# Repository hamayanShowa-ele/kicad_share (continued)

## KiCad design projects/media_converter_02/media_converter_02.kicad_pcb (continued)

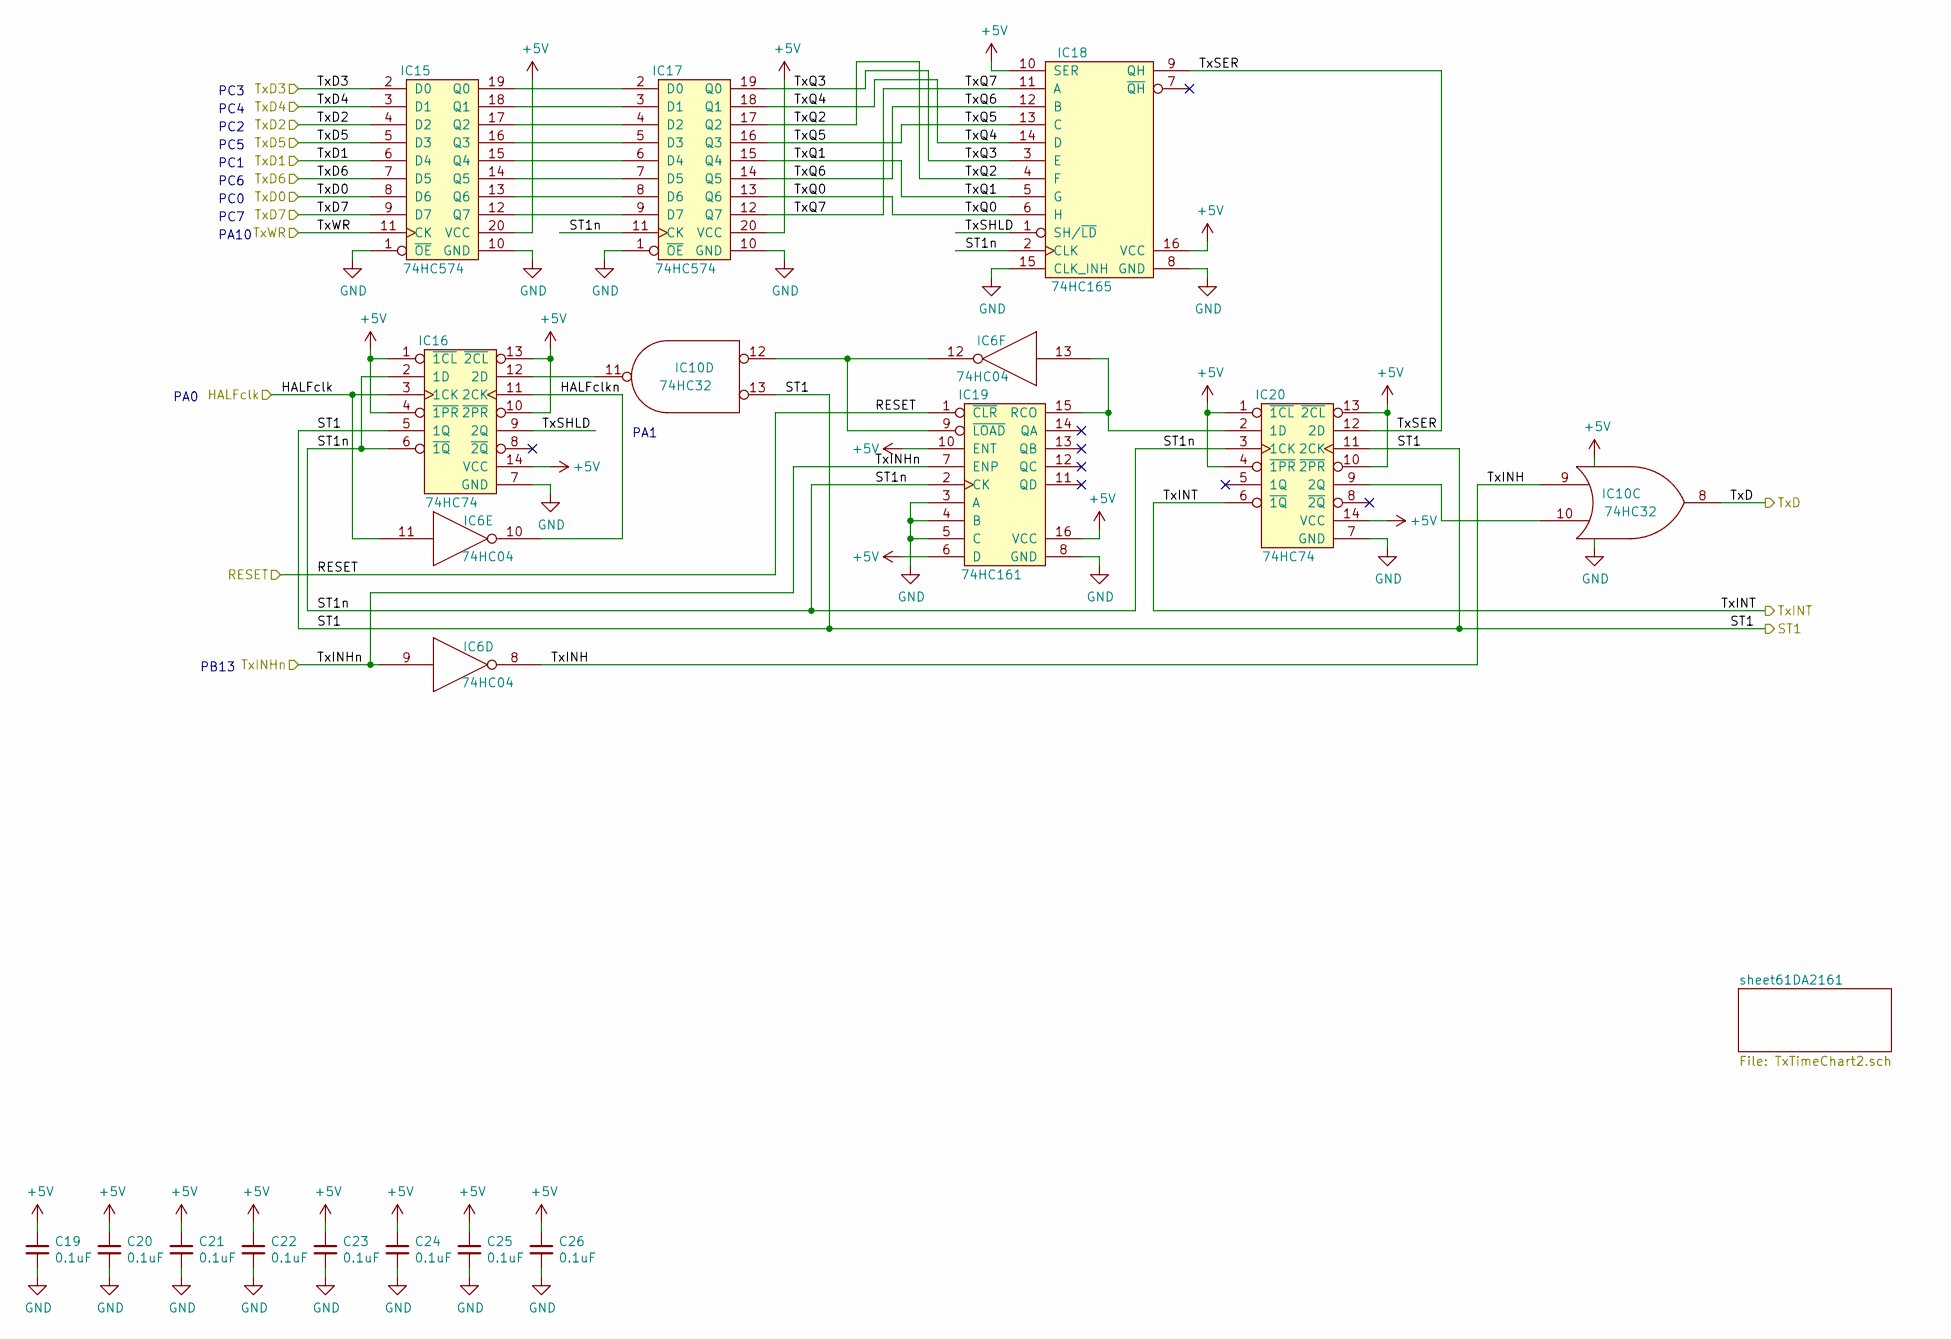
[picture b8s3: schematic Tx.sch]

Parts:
C19, C20, C21, C22, C23, C24, C25, C26: 0.1uF; C_0603
IC6: 74HC04; IC_DIP-14_W7.62mm
IC10: 74HC32; IC_DIP-14_W7.62mm
IC15, IC17: 74HC574; ic_DIP-20_W7.62mm
IC16, IC20: 74HC74; IC_DIP-14_W7.62mm
IC18: 74HC165; ic_DIP-16_W7.62mm
IC19: 74HC161; ic_DIP-16_W7.62mm

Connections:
+5V: C19.1, C20.1, C21.1, C22.1, C23.1, C24.1, C25.1, C26.1, IC6.14 (VCC), IC10.14 (VCC), IC15.20 (VCC), IC16.1 (~1CL), IC16.4 (~1PR), IC16.10 (~2PR), IC16.13 (~2CL), IC16.14 (VCC), IC17.20 (VCC), IC18.10 (SER), IC18.16 (VCC), IC19.6 (D), IC19.10 (ENT), IC19.16 (VCC), IC20.1 (~1CL), IC20.4 (~1PR), IC20.10 (~2PR), IC20.13 (~2CL), IC20.14 (VCC); also elsewhere on the board
/HALFclk: IC6.11, IC16.3 (1CK); also elsewhere on the board
/RSTn: IC19.1 (~CLR); also elsewhere on the board
/ST1: IC10.13, IC16.5 (1Q), IC20.11 (2CK); also elsewhere on the board
/Tx/HALFclkn: IC6.10, IC16.11 (2CK)
/Tx/ST1n: IC16.2 (1D), IC16.6 (~1Q), IC17.11 (CK), IC18.2 (CLK), IC19.2 (CK), IC20.3 (1CK)
/Tx/TxINH: IC6.8, IC10.9
/Tx/TxQ0: IC17.13 (Q6), IC18.6 (H)
/Tx/TxQ1: IC17.15 (Q4), IC18.5 (G)
/Tx/TxQ2: IC17.17 (Q2), IC18.4 (F)
/Tx/TxQ3: IC17.19 (Q0), IC18.3 (E)
/Tx/TxQ4: IC17.18 (Q1), IC18.14 (D)
/Tx/TxQ5: IC17.16 (Q3), IC18.13 (C)
/Tx/TxQ6: IC17.14 (Q5), IC18.12 (B)
/Tx/TxQ7: IC17.12 (Q7), IC18.11 (A)
/Tx/TxSER: IC18.9 (QH), IC20.12 (2D)
/Tx/TxSHLD: IC16.9 (2Q), IC18.1 (SH/~LD)
/TxD: IC10.8; also elsewhere on the board
/TxD0: IC15.8 (D6); also elsewhere on the board
/TxD1: IC15.6 (D4); also elsewhere on the board
/TxD2: IC15.4 (D2); also elsewhere on the board
/TxD3: IC15.2 (D0); also elsewhere on the board
/TxD4: IC15.3 (D1); also elsewhere on the board
/TxD5: IC15.5 (D3); also elsewhere on the board
/TxD6: IC15.7 (D5); also elsewhere on the board
/TxD7: IC15.9 (D7); also elsewhere on the board
/TxINHn: IC6.9, IC19.7 (ENP); also elsewhere on the board
/TxINT: IC20.6 (~1Q); also elsewhere on the board
/TxWR: IC15.11 (CK); also elsewhere on the board
GND: C19.2, C20.2, C21.2, C22.2, C23.2, C24.2, C25.2, C26.2, IC6.7 (GNDA), IC10.7 (GND), IC15.1 (~OE), IC15.10 (GND), IC16.7 (GND), IC17.1 (~OE), IC17.10 (GND), IC18.8 (GND), IC18.15 (CLK_INH), IC19.3 (A), IC19.4 (B), IC19.5 (C), IC19.8 (GND), IC20.7 (GND); also elsewhere on the board
unnamed: IC10.10, IC20.9 (2Q)
unnamed: IC10.11, IC16.12 (2D)
unnamed: IC6.12, IC10.12, IC19.9 (~LOAD)
unnamed: IC15.12 (Q7), IC17.9 (D7)
unnamed: IC15.13 (Q6), IC17.8 (D6)
unnamed: IC15.14 (Q5), IC17.7 (D5)
unnamed: IC15.15 (Q4), IC17.6 (D4)
unnamed: IC15.16 (Q3), IC17.5 (D3)
unnamed: IC15.17 (Q2), IC17.4 (D2)
unnamed: IC15.18 (Q1), IC17.3 (D1)
unnamed: IC15.19 (Q0), IC17.2 (D0)
unnamed: IC6.13, IC19.15 (RCO), IC20.2 (1D)

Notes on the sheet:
PA0
PA1
PA10
PC7
PC6
PC5
PC4
PC3
PC2
PC1
PC0
PB13

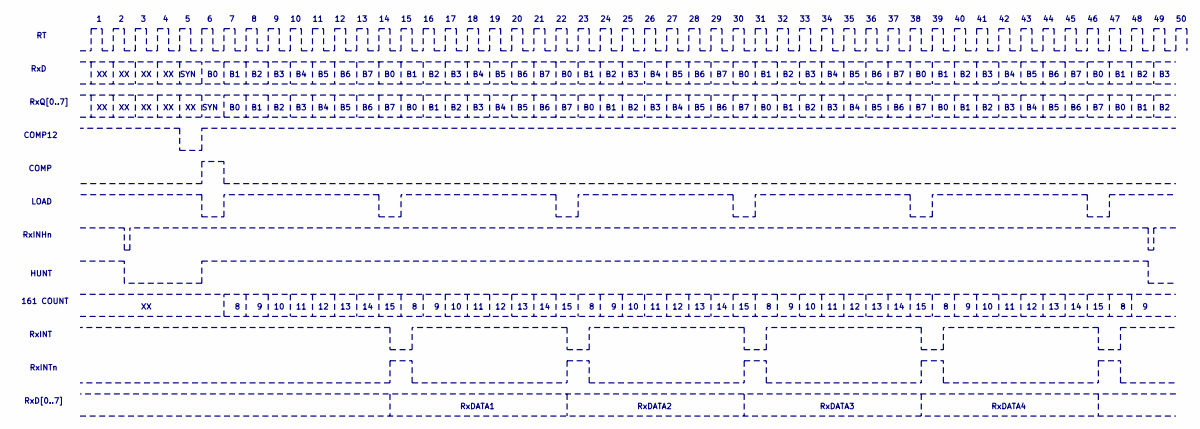
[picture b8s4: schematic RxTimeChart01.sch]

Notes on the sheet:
COMP12
161 COUNT
LOAD
HUNT
RxD
SYN
RxQ[0..7]
RxINT
RxINTn
RxDATA1
RxDATA2
RxDATA3
RxDATA4
RxD[0..7]
RxINHn
COMP

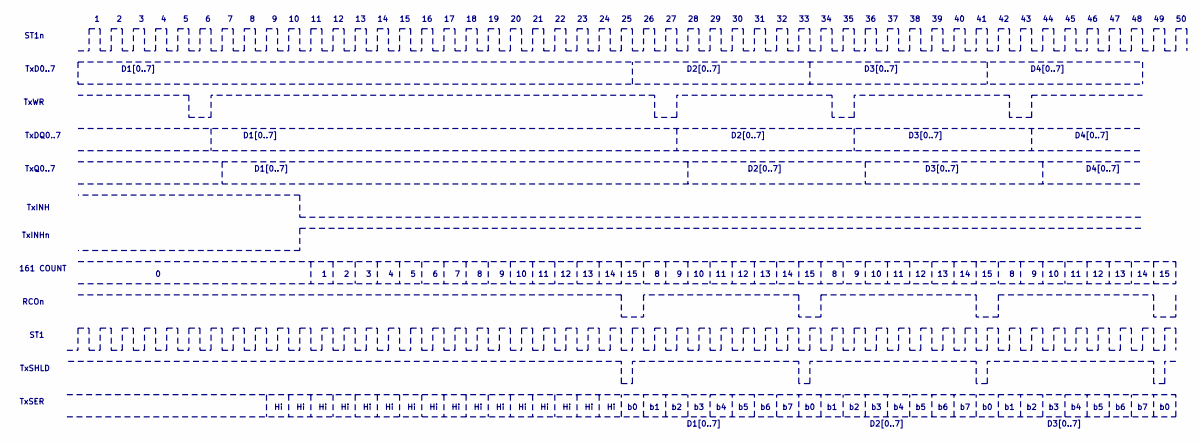
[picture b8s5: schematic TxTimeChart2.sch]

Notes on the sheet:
ST1n
TxD0..7
D1[0..7]
TxWR
TxDQ0..7
TxQ0..7
TxINH
TxINHn
161 COUNT
RCOn
ST1
TxSHLD
TxSER
D2[0..7]
D3[0..7]
D4[0..7]

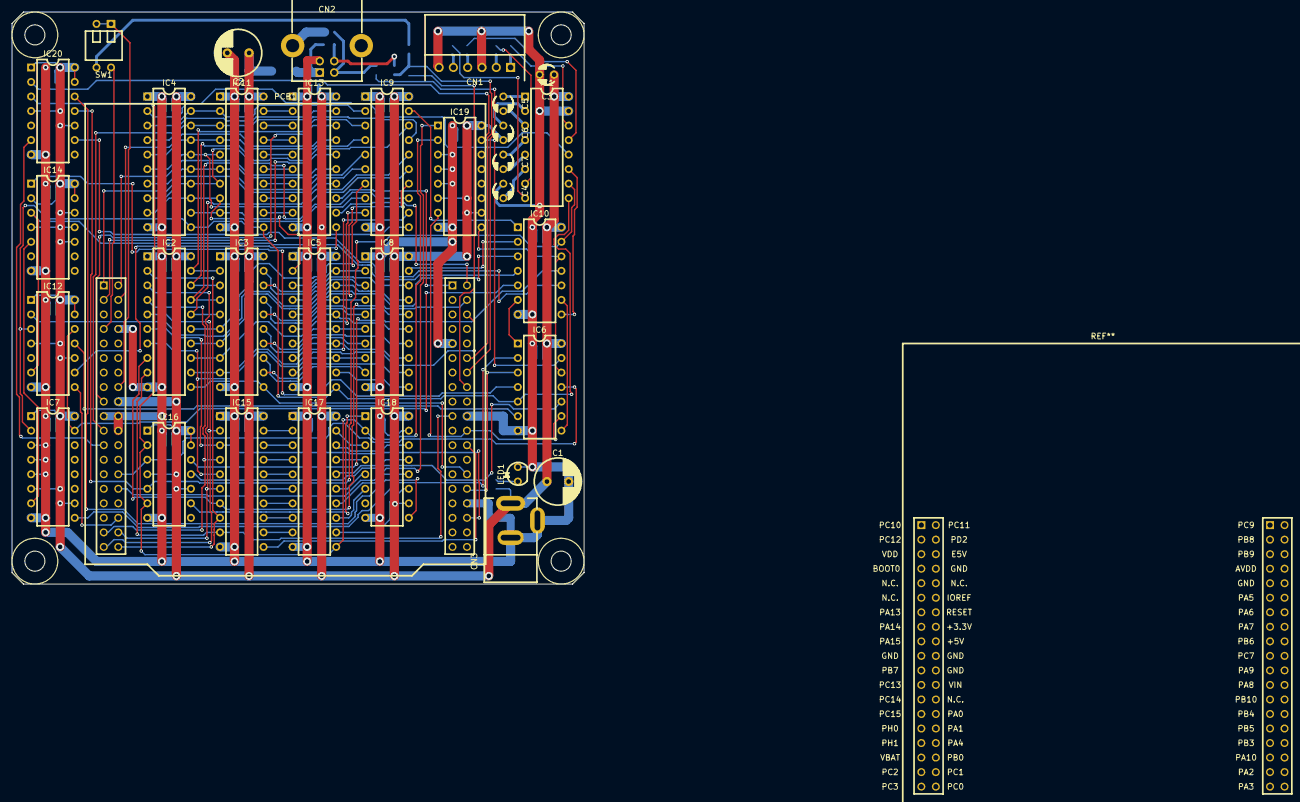
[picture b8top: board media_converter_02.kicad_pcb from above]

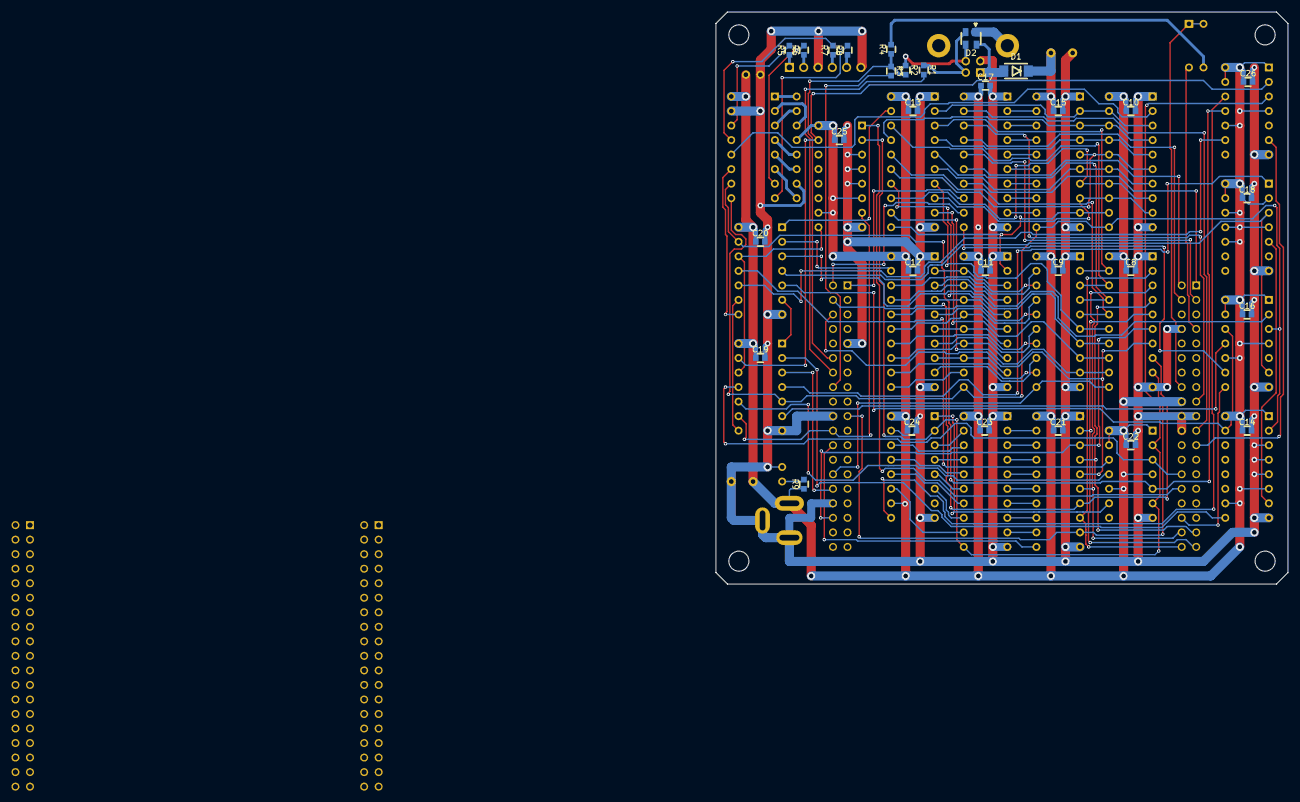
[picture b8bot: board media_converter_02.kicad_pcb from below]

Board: 2 copper layers, 100.0 x 100.0 mm, 63 parts (30 on the bottom side), 131 nets.
